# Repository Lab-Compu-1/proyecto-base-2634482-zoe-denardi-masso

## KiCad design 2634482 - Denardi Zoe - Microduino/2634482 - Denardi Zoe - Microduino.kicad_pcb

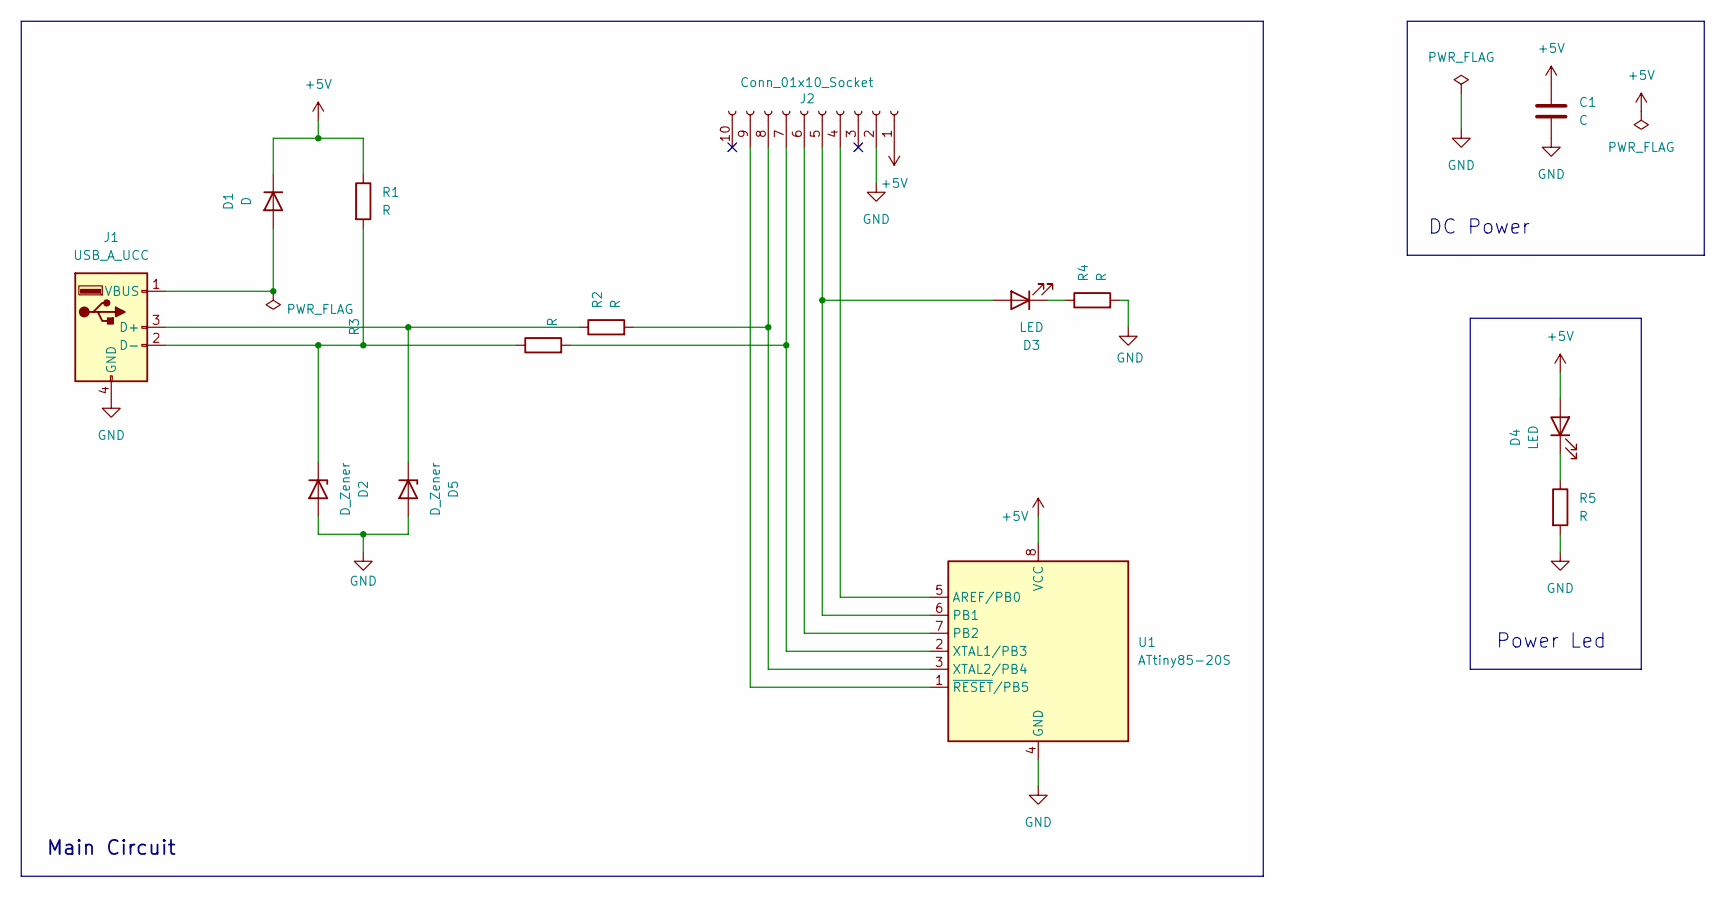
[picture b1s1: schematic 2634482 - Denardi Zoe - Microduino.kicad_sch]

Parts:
C1: C; C_0805_2012Metric_Pad1.18x1.45mm_HandSolder
D1: D; D_MELF_Handsoldering
D2, D5: D_Zener; D_SOD-123
D3: LED; LED_0805_2012Metric_Pad1.15x1.40mm_HandSolder
D4: LED; LED_1206_3216Metric_Pad1.42x1.75mm_HandSolder
J1: USB_A_UCC
J2: Conn_01x10_Socket; PinSocket_1x10_P2.54mm_Vertical
R1, R2, R3, R4, R5: R; R_0805_2012Metric_Pad1.20x1.40mm_HandSolder
U1: ATtiny85-20S; SOIC-8_5.3x5.3mm_P1.27mm

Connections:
+5V: C1.1, D1.1 (K), D4.2 (A), J2.1, R1.1, U1.8 (VCC)
GND: C1.2, D2.2 (A), D5.2 (A), J1.4 (GND), J2.2, R4.2, R5.2, U1.4 (GND)
unnamed: D1.2 (A), J1.1 (VBUS)
unnamed: D2.1 (K), J1.2 (D-), R1.2, R3.1
unnamed: D3.2 (A), J2.5, U1.6 (PB1)
unnamed: D3.1 (K), R4.1
unnamed: D4.1 (K), R5.1
unnamed: D5.1 (K), J1.3 (D+), R2.1
unnamed: J2.4, U1.5 (AREF/PB0)
unnamed: J2.6, U1.7 (PB2)
unnamed: J2.7, R3.2, U1.2 (XTAL1/PB3)
unnamed: J2.8, R2.2, U1.3 (XTAL2/PB4)
unnamed: J2.9, U1.1 (~RESET/PB5)

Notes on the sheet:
Power Led
Main Circuit
DC Power

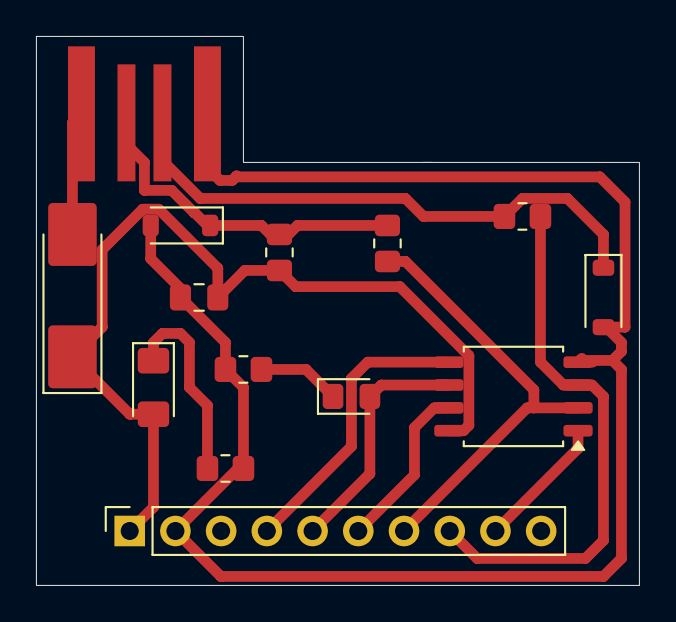
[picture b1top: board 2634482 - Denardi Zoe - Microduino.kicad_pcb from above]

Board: 2 copper layers, 33.5 x 30.5 mm, 14 parts (0 on the bottom side), 13 nets.

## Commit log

2026-05-22 GitHub Classroom Feedback
2026-05-22 Setting up GitHub Classroom Feedback
2026-05-29 Mi primer commit y entrega de proyecto KiCad
2026-06-05 Entrega final
